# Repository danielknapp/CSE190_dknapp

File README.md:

# CSE190_dknapp
Daniel Knapp's github repository for the UCSE Spring CSE 190 Quadcoptor class

Lab 1:
Worked with Trevor Smith on this lab. The files pertaining to the lab should be on his repository https://github.com/trevorsm7/CSE190_tsmith.git.

Lab 2:
The lab files should be in LabReports/Lab2.

Lab 3:
The lab files should be in LabReports/Lab3. I worked with Matt Asaro on this lab.

Lab 4:
The lab files should be in LabReports/Lab4. "workingDir" can be ignored.

Lab 5:
Worked with James Lee on this lab. The files should be in his respository at https://github.com/batmanatucsd/quadcopter.git

Lab 6:
I worked with the same person as on lab 5.

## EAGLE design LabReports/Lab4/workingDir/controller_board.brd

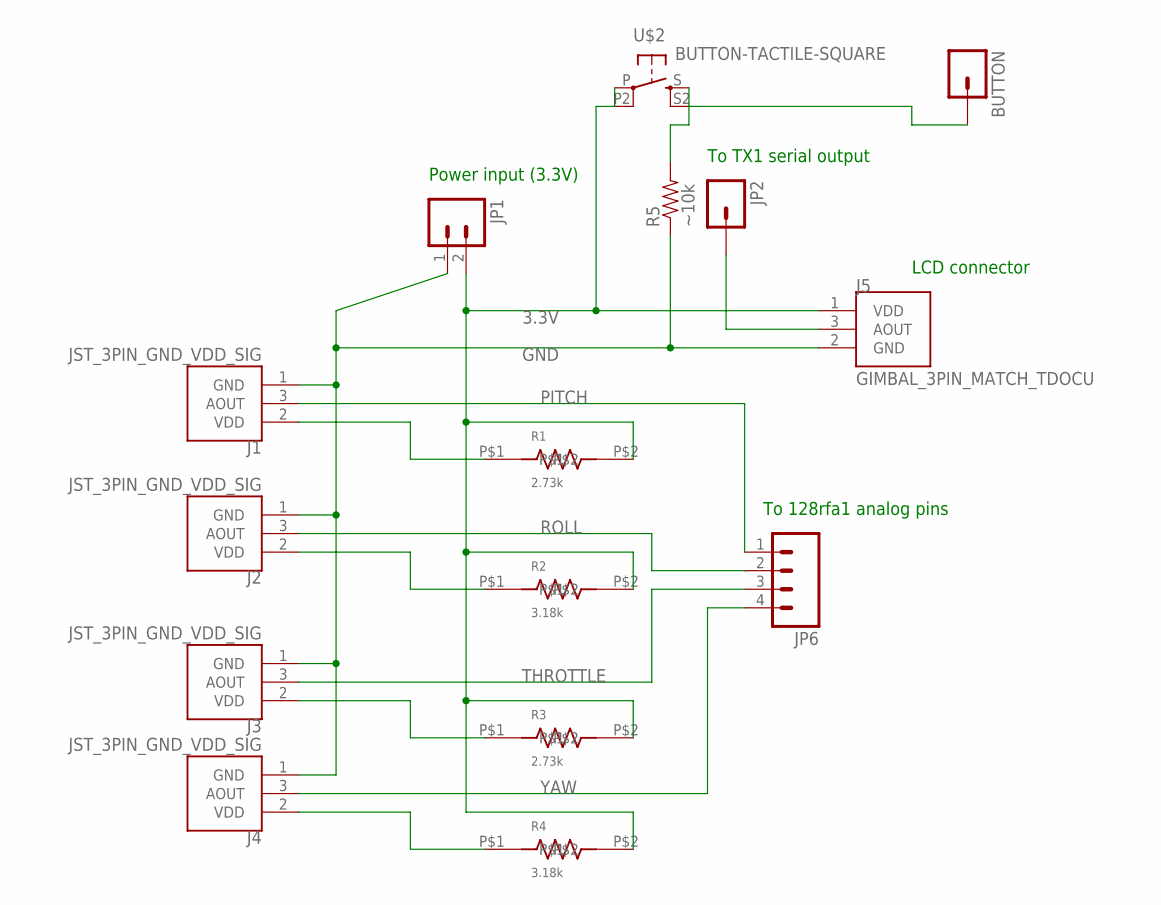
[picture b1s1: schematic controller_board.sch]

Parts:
BUTTON: M01PTH; 1X01
J1, J2, J3, J4: JST_3PIN_GND_VDD_SIG; JST-3-PTH-REVERSE
J5: GIMBAL_3PIN_MATCH_TDOCU; JST-3-PTH
JP1: M021X02_NO_SILK; 1X02_NO_SILK
JP2: M01PTH; 1X01
JP6: M04PTH; 1X04
R1, R3: 2.73k; CRF12
R2, R4: 3.18k; CRF12
R5: ~10k; AXIAL-0.4
U$2: BUTTON-TACTILE-SQUARE; BUTTON-TACTILE-SQUARE-ADAFRUIT1010

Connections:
3.3V: J5.1 (VDD), JP1.2, R1.P$2, R2.P$2, R3.P$2, R4.P$2, U$2.P, U$2.P2 (P1)
GND: J1.1 (GND), J2.1 (GND), J3.1 (GND), J4.1 (GND), J5.2 (GND), JP1.1, R5.P$1 (1)
unnamed: J1.2 (VDD), R1.P$1
unnamed: J2.2 (VDD), R2.P$1
unnamed: J3.2 (VDD), R3.P$1
unnamed: J4.2 (VDD), R4.P$1
unnamed: BUTTON.1, R5.P$2 (2), U$2.S, U$2.S2 (S1)
unnamed: J5.3 (AOUT), JP2.1
PITCH: J1.3 (AOUT), JP6.1
ROLL: J2.3 (AOUT), JP6.2
THROTTLE: J3.3 (AOUT), JP6.3
YAW: J4.3 (AOUT), JP6.4

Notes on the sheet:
To 128rfa1 analog pins
LCD connector
Power input (3.3V)
To TX1 serial output

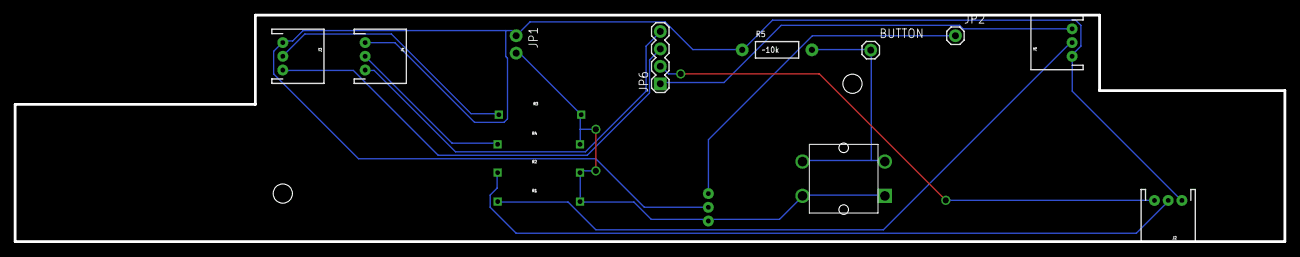
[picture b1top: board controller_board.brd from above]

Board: 2 copper layers, 185.0 x 33.0 mm, 16 parts (1 on the bottom side), 12 nets.

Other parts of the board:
U$1: CONNECTOR_BOARD_OUTLINE

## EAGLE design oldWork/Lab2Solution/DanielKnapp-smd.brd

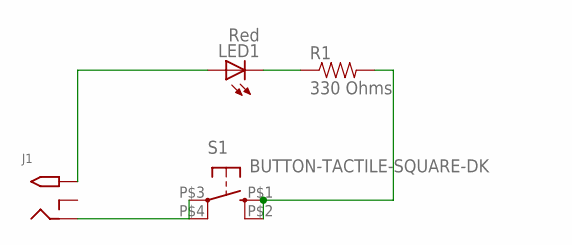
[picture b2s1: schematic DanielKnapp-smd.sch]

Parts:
J1: 2.1MMJACKTHM; PJ-102A
LED1: Red; LED5MM
R1: 330 Ohms; AXIAL-0.3
S1: BUTTON-TACTILE-SQUARE-DK

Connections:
unnamed: LED1.K (C), R1.P$1 (1)
unnamed: R1.P$2 (2), S1.P$1 (S), S1.P$2 (S1)
unnamed: J1.RING, S1.P$3, S1.P$4 (P1)
unnamed: J1.TIP, LED1.A

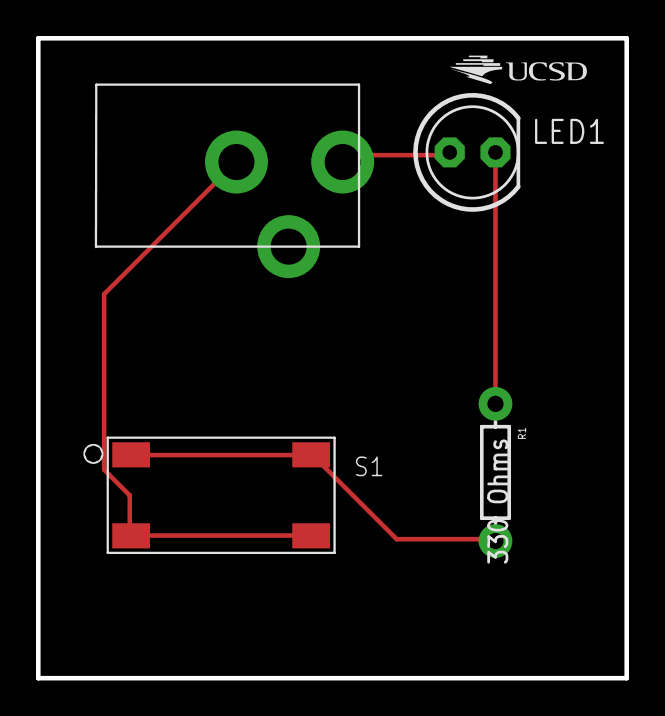
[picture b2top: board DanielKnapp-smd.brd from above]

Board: 2 copper layers, 32.7 x 35.5 mm, 5 parts (0 on the bottom side), 4 nets.

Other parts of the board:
U$1: UCSD_LOGO

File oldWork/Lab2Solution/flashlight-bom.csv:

Partlist exported from C:/Users/danny/Documents/GitHub/CSE190_dknapp/Lab2Solution/Lab2Sol.sch at 4/8/2015 4:00:21 PM

Qty Value                 Device                Package                            Parts Description                                                                              
1   2.1MMJACKTHM          2.1MMJACKTHM          PJ-102A                            J1    2.1mm x 5.5mm THM DC jack with internal switch. Digikey part #PJ-102A, 4UCON part #05537 
1   330 Ohms              RESISTORAXIAL-0.3     AXIAL-0.3                          R1    Resistor                                                                                 
1   BUTTON-TACTILE-SQUARE BUTTON-TACTILE-SQUARE BUTTON-TACTILE-SQUARE-ADAFRUIT1010 S1                                                                                             
1   Red                   LED5MM                LED5MM                             LED1  LED

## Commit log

2015-04-03 Updated README with Lab 1 administrative details
2015-04-09 Completed Lab 2
2015-04-09 Updated README for Lab 2
2015-04-14 Everything for Lab 3 should be in the LabReports/Lab3 folder except for the writeup.
2015-04-14 Added lab writeup pdf
2015-04-14 compressed pdf
2015-04-15 Rearranged Folder Structure
2015-04-17 Finished Lab 4
    Hopefully all that was needed to be done with lab 4 is completed and the
    files are in the LabReports/Lab4 directory.
2015-04-28 Changed Library And Pointed README To Lab 5
2015-05-08 Changed README

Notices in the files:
parts and their libraries:
SparkFun-Connectors: Licensing: Creative Commons ShareAlike 4.0 International - https://creativecommons.org/licenses/by-sa/4.0
